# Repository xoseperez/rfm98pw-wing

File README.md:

# RFM98PW Wing

This is an Adafruit Feather (TM) compatible Wing for the RFM98PW LoRa radio module by HopeRF that works at 169MHz.

## Images

## License

This design is under [CreativeCommons Attribution-ShareAlike 4.0 International License](https://choosealicense.com/licenses/cc-by-sa-4.0).

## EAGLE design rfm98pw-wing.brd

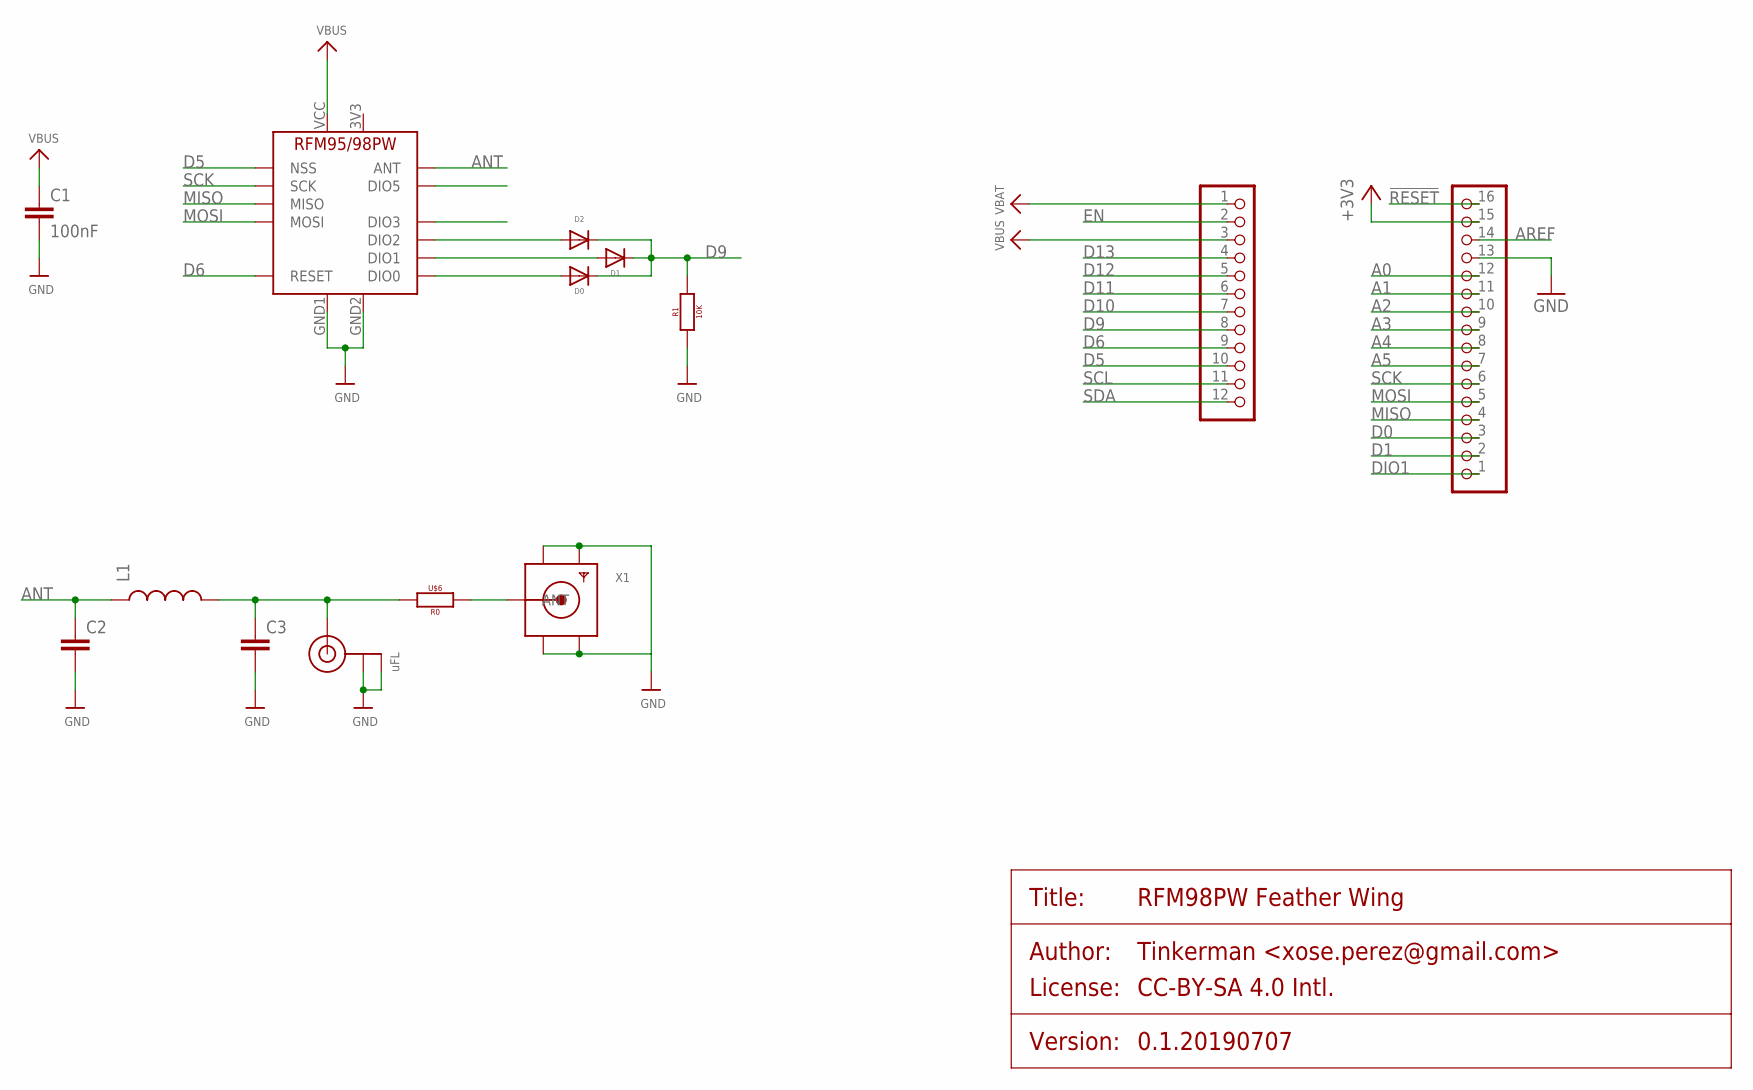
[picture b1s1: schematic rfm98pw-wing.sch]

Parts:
C1: 100nF; C0805K
C2, C3: C-EUC0805K; C0805K
D0, D1, D2: DIODE-SMD; 0805_DIODE
JP1: HEADER-1X16ROUND; 1X16_ROUND
JP3: HEADER-1X12; 1X12_ROUND
L1: INDUCTOR-SPARKFUN0805; 0805
R1: 10K; 0805
U$6: R0; 0805
U$24: RFM95PW-RFM98PW
X1: SMACONNECTOR_EDGE; SMA_EDGELAUNCH
X4: uFL; U.FL

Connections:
3V3: U$24.3V3
!RESET: JP1.16
+3V3: JP1.15
A0: JP1.12
A1: JP1.11
A2: JP1.10
A3: JP1.9
A4: JP1.8
A5: JP1.7
ANT: C2.1, L1.1, U$24.ANT
ANT1: U$6.2, X1.P (ANT)
AREF: JP1.14
D0: JP1.3
D1: JP1.2
D5: JP3.10, U$24.NSS
D6: JP3.9, U$24.RESET
D9: D0.C, D1.C, D2.C, JP3.8, R1.2
D10: JP3.7
D11: JP3.6
D12: JP3.5
D13: JP3.4
DIO1: JP1.1
EN: JP3.2
GND: C1.2, C2.2, C3.2, JP1.13, R1.1, U$24.GND1, U$24.GND2, X1.GND@1 (GND4), X1.GND@2 (GND3), X1.GND@3 (GND2), X1.GND@4 (GND1), X4.1 (GND), X4.2 (GND)
MISO: JP1.4, U$24.MISO
MOSI: JP1.5, U$24.MOSI
unnamed: D0.A, U$24.DIO0
unnamed: D1.A, U$24.DIO1
unnamed: D2.A, U$24.DIO2
unnamed: C3.1, L1.2, U$6.1, X4.3 (SIGNAL)
SCK: JP1.6, U$24.SCK
SCL: JP3.11
SDA: JP3.12
VBAT: JP3.1
VBUS: C1.1, JP3.3, U$24.VCC

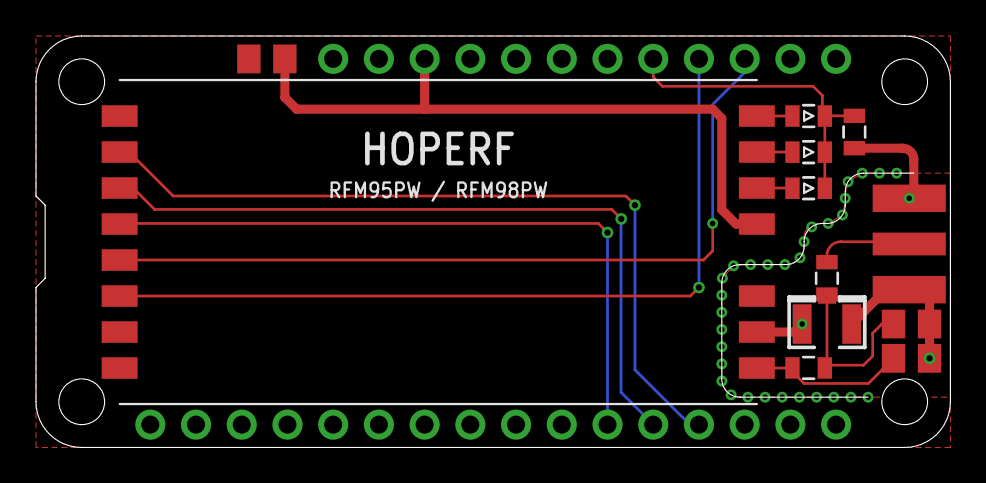
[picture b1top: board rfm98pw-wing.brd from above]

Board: 2 copper layers, 50.8 x 22.9 mm, 14 parts (0 on the bottom side), 14 nets.

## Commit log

2019-07-07 Images and license
2019-07-07 Add RFM98PW datasheet

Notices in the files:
rfm98pw-wing.sch:
PROJECT_LICENSE: CC-BY-SA 4.0 Intl.
parts and their libraries:
microbuilder: This work is placed in the public domain, and may be freely used for commercial and non-commercial work with the following conditions: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
